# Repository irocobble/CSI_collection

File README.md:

# Human Presence Detection using Wi-Fi CSI

**Team Name: Irocobble_Team** 

## AIM
To develop a prototype device that can sense human presence in a site of interest without using cameras, wearables, or expensive radar hardware. This is achieved by analyzing how Wi-Fi signals change when a person is present.

---

## Research Path — What We Tried First

To achieve human presence detection, our team initially explored IoT devices to detect presence.

1.  **DFRobot C4001 (24 GHz FMCW radar):** This uses a remarkably high frequency of 24 GHz to sense human presence. It works by sending an electromagnetic wave at 24 GHz, and when it reflects back and is captured by the sensor, the wave gets induced by a phase difference. We thought this small phase difference would be enough to accurately detect a human, but these devices require an extremely clean environment to function properly.
2.  **Secondary FMCW IoT Sensor:** We tried a similar IoT device, but it was equally ineffective. Both devices operated on **FMCW (Frequency Modulated Continuous Wave)**. We advise avoiding this approach as it becomes very complicated, although ECE students interested in this can explore it further.

**The Breakthrough:** After failing to extract useful information from these radar devices, we dove deeper and found our solution: **CSI data**.

---

## How It Works — The Big Picture

The system follows a specific pipeline:

**ESP32-S3** → **CSI matrix** → **Spectrogram image** → **EfficientNetV2** → **Activity label** → **Dashboard**

A Wi-Fi router sends signals continuously. The ESP32-S3 acts as the receiver and measures exactly how those signals change as they bounce around the room. When a human moves, they disturb the signal in a unique way. We convert that disturbance into an image (spectrogram) and classify it using a neural network.

---

## Key Definitions

* **CSI (Channel State Information):** Detailed information about how a Wi-Fi signal travels from transmitter to receiver. Unlike RSSI, CSI captures amplitude, phase, and frequency response across every individual subcarrier, providing a rich fingerprint of the environment.
* **OFDM Subcarrier:** Wi-Fi splits its signal into many narrow frequency bands called subcarriers. The ESP32-S3 exposes 52 of them. Each is affected differently by objects in the room, making CSI highly informative.
* **RSSI (Received Signal Strength Indicator):** A single number representing received Wi-Fi signal strength. It is too coarse for detecting subtle human presence compared to CSI.
* **Multipath Propagation:** Wi-Fi signals reflect off walls, furniture, and people, arriving at the receiver via multiple paths. CSI captures all these reflections simultaneously, making it sensitive to human movement.
* **LOS / NLOS (Line-of-Sight / Non-Line-of-Sight):** LOS means a direct path between transmitter and receiver. NLOS means an obstruction blocks the path. Our system works reliably in both conditions.
* **STFT (Short-Time Fourier Transform):** A mathematical tool that converts a 1D signal into a 2D time-frequency image called a spectrogram.
* **Spectrogram:** A grayscale image (52 × 400 pixels in our system) where each column is a snapshot in time and each row is one of the 52 subcarriers. Pixel intensity represents signal amplitude.
* **EfficientNetV2:** A state-of-the-art Convolutional Neural Network (CNN) modified to accept single-channel grayscale spectrograms and retrained on our CSI dataset.
* **FreeRTOS:** A real-time operating system for microcontrollers that lets the ESP32 run tasks concurrently (capturing CSI and sending data over UART) safely.
* **CRC-16/CCITT:** A checksum algorithm that detects transmission errors to ensure clean data enters the pipeline.
* **Hampel Filter:** A statistical outlier-removal filter that replaces sudden noise spikes in the CSI data before transmission.
* **WeightedRandomSampler:** A PyTorch training utility that ensures the model sees each activity class equally often during training to prevent bias.
* **Supabase:** An open-source database used to log every inference result and store spectrogram images.

---

## Hardware

### Why ESP32?
While chips like the Artemis series, BCM series, and some Intel Wi-Fi cards expose CSI, we chose the ESP32 family because it is inexpensive, well-documented, and supported by ESP-IDF (which provides direct access to the CSI callback API).

Our first-generation capture rig used four off-the-shelf ESP32-S3 WROOM modules. We have since designed a **custom dual-receiver PCB** to replace them, described below.

### Custom Dual-Receiver CSI Board (Rev. 2)

Off-the-shelf dev boards proved to be the limiting factor in CSI quality. Their PCB antennas cannot be replaced, their ground planes are shared with USB and power circuitry, and every unit sits on a separate USB cable with its own power supply — all of which inject amplitude noise into exactly the measurement we care about. The custom board addresses each of these.

**Two independent receivers on one board.** Both ESP32s operate in receive-only mode and capture CSI from the same ambient Wi-Fi traffic, giving two spatially separated measurements of the same environment from a single unit.

**Key specifications**

| Item | Detail |
|---|---|
| Board | 4-layer, 55 × 55 mm |
| Stackup | F.Cu / 0.12 mm 2116 prepreg / **In1.Cu solid GND** / 1.165 mm core / **In2.Cu +3V3** / 0.12 mm / B.Cu |
| MCUs | 2 × ESP32, each with its own 40 MHz crystal and AT25SF081 SPI flash |
| Antennas | 2 × SMA connector for external antennas (bi-quad or other) |
| RF feed | 50 Ω controlled-impedance microstrip, 0.20 mm wide |
| Matching | Pi network (1.5 pF / 2 nH / 1.5 pF) per channel, with spare DNP positions for bench tuning |
| USB | USB-C → CH334F hub → 2 × CP2102N UART bridges (one COM port per ESP32) |
| Power | AP63203 buck (5 V → 3.3 V), 2 A polyfuse, PMEG2020EH reverse-protection Schottky |
| Protection | USBLC6-4SC6 ESD array on USB data lines, ESD diodes on EN/BOOT |
| Programming | Cross-coupled DTR/RTS auto-reset per channel (standard esptool circuit) |
| Draw | ~290 mA at 5 V with both receivers active — within the 500 mA USB budget |

**Why the layer stack matters.** A dedicated uninterrupted ground plane 0.12 mm below the signal layer gives every RF and USB trace a clean return path. Nothing is routed on the ground layer. Via inductance from any component to ground is roughly 0.04 nH, so the antenna matching network behaves as designed rather than being swamped by parasitics.

**Antenna launch design.** Each SMA connector is surrounded by a ring of ground vias so the return current reaches the plane immediately. A deliberate void in the ground plane beneath each SMA signal pad removes ~2.3 pF of parasitic capacitance that would otherwise present a 12 Ω discontinuity at the connector. Measured effect: launch insertion loss drops from ~3.3 dB to ~0.1 dB per channel, and both channels are symmetric to within a few tenths of a dB — important when comparing amplitude between the two receivers.

**Single power source.** Both receivers share one regulated 3.3 V rail from a single USB connection, rather than two separately powered dev boards. One cable, one supply, one ground reference.

**Custom Bi-Quad Antenna:** A custom-designed 2.4 GHz directional antenna connects via the SMA ports to provide higher gain and improved CSI stability than a stock PCB antenna.

**Source code and hardware files:** [github.com/irocobble/CSI_collection](https://github.com/irocobble/CSI_collection/tree/main)

### Known Design Limitations

Documented deliberately so future revisions can address them:

* **No cross-receiver phase coherence.** The two ESP32s run from independent crystals, so their carrier and sampling frequency offsets drift relative to each other. This is fine for our amplitude-only pipeline but rules out phase-based techniques such as AoA or MUSIC across the two antennas. A shared 40 MHz TCXO feeding both `XTAL_P` pins would fix this in a future revision.
* **No GPIO breakout.** No general-purpose pins are brought out, so there is no hardware trigger, PPS input, or sync line for correlating CSI against external ground truth. Timestamping is currently done in software over USB.
* **1 MB flash (AT25SF081).** Sufficient for the capture firmware but leaves no room for OTA update partitions.

### Bring-Up Checklist

For anyone assembling a board, test in this order and stop at the first failure — it localises the fault far faster than powering everything at once:

1. **Power only**, no USB data — confirm 3.3 V, check input voltage at the buck, scope the rail for ripple.
2. **Plug USB** — does the hub enumerate? If not, fit the DNP crystal load capacitors (C4/C23, 12 pF).
3. **Check both COM ports appear.** A missing port isolates to that CP2102N or its hub port.
4. **Flash each ESP32** — auto-reset should work without holding buttons.
5. **Scope VDD3P3 during RX.** More than ~50 mV of ripple → populate C8/C42 (1 µF).
6. **VNA the antenna ports** and tune the pi network. This step determines CSI amplitude quality more than anything else.
7. **Capture CSI** and inspect the noise floor across all 52 subcarriers before trusting any measurement.

Keep spare 12 pF 0402, 1 µF 0603, and 12 pF-load 40 MHz crystals on hand for steps 2, 5, and any oscillator trouble.

---

## Firmware — ESP-IDF Setup

### Installation

**Linux**
1.  Make a new directory: `mkdir -p ~/esp`
2.  Get to the directory: `cd ~/esp`
3.  Clone the files from the official ESP git repo:
    `git clone --recursive https://github.com/espressif/esp-idf.git`
4.  Get in the directory: `cd esp-idf`
5.  Install the esp-idf: `./install.sh`

**Windows**
1.  Go to: [https://dl.espressif.com/dl/esp-idf/](https://dl.espressif.com/dl/esp-idf/)
2.  Download and install the universal online installer.

### Activating The Environment
1.  Activate the esp-IDE environment by running export.sh:
    `source ~/esp/esp-idf/export.sh` (Run once per terminal session)
2.  Go to the esp directory: `cd ~/esp`
3.  Run to create an ESP Project: `idf.py create-project my_project`
4.  Go to Project Directory: `cd my_project`

### Required Project File Structure (Crucial!)
The project must follow this layout exactly:

```
my_project/
├── CMakeLists.txt      # lists component directories
├── sdkconfig           # auto-generated after menuconfig
└── main/
    ├── CMakeLists.txt  # registers main.c as a component
    └── main.c          # your application code
```

### Menuconfig (The Heart of ESP-IDE)
Run: `idf.py menuconfig`
Common configurations for this project:
* **Enable CSI:** Component config → Wi-Fi → [*] Enable CSI
* **SSID + Password:** Wi-Fi settings → set the SSID and password.

### Build, Flash, and Monitor
1.  Activate ESP-IDE on bash.
2.  Set the chip target — this **must** match the silicon on the board:
    `idf.py set-target esp32` (use `esp32s3` for the older WROOM-module rig)
3.  Go to the root directory of the Project.
4.  Compile: `idf.py build`
5.  Flash: `idf.py -p /dev/ttyUSB0 flash` (replace port as needed)
6.  Monitor Serial Output: `idf.py monitor` (Ctrl+] to exit)

**Note on the custom board:** it presents **two** serial ports, one per receiver. Flash each independently, e.g. `/dev/ttyUSB0` and `/dev/ttyUSB1`.

### How the Firmware Works
The firmware runs two concurrent FreeRTOS tasks:
1.  **CSI callback:** Fires on every received Wi-Fi packet. Extracts the amplitude of 52 subcarriers, applies a Hampel filter to remove spike outliers, and writes the cleaned sample into a shared frame buffer protected by a FreeRTOS mutex.
2.  **UART TX task:** Once 400 samples accumulate (forming a 52×400 frame), it wraps the payload, computes a CRC-16/CCITT checksum, and transmits at 921,600 baud.

---

## Software Pipeline — Python

### Overview
**Serial read** → **CRC validation** → **Reshape 52×400** → **PNG export** → **API inference** → **Supabase log** → **Dashboard**

* **Serial Ingestion:** A `FrameReader` class maintains a buffer and scans for frames, validating the CRC-16 checksum to ensure clean data.
* **Multi-device Auto-detection:** A background thread scans COM ports to automatically detect active ESP32 units. On the custom board this discovers both on-board receivers as separate ports.
* **Image Construction:** The ESP-32 provides CSI data as a matrix. We convert this 52×400 matrix (200 samples in X-axis and 52 amplitude values in Y-axis) into a 52*400 image. The black and white density represents the amplitude change.
* **Asynchronous Inference & Re-inference:** Python handles real-time inference via an API without blocking the serial reader and includes a GUI for manual re-inference on previously captured frames.

---

## Machine Learning Pipeline

### Dataset
A custom dataset was collected using the four ESP32-S3 units in real indoor environments (LOS and NLOS).
* **Labels:** `trainLabels.csv`, `validationLabels.csv`, `testLabels.csv`
* **Normalization:** `meanStd.csv` is used to apply identical normalization `(x − mean) / std`.

> **Note:** Data captured on the custom board has a different RF front end (external antenna, different ground reference, different launch loss) from the WROOM-module rig. Recompute `meanStd.csv` for the new hardware, and treat the two sources as separate domains until a mixed-hardware model is validated.

### Preprocessing and Augmentation
1.  Grayscale conversion
2.  Tensor conversion ([0, 255] to [0, 1])
3.  Normalization
4.  Random circular shift (training only)
5.  Gaussian noise injection (training only)

### Model (The AI-ML Part)
**Backbone:** EfficientNetV2-S. This is a lightweight, efficient CNN that helps us find key details in the small images we generate. The first convolution layer is modified to accept 1-channel (grayscale) input.

### Training Configuration
* **Loss function:** CrossEntropyLoss
* **Optimiser:** Adam (LR: 0.0001)
* **LR scheduler:** ReduceLROnPlateau
* **Early stopping:** Halts if validation accuracy does not improve for 20 epochs.
* **Class balancing:** WeightedRandomSampler
* **Hardware:** NVIDIA RTX 4060 with CUDA, via PyTorch.

---

## System Integration
* **Flask REST API:** Inference results are served via a Flask REST endpoint.
* **Real-time Web Dashboard:** Displays current activity label and confidence score.
* **Flutter Mobile App:** Cross-platform mobile application mirroring the dashboard.
* **Supabase Cloud Logging:** Every inference result and image is asynchronously inserted into a Supabase Postgres table and storage bucket.

---

## Limitations and Future Work

**Current limitations:** The CNN treats the spectrogram as a static image without explicitly modeling temporal sequences. Performance varies between LOS and NLOS environments when trained exclusively on one. The dataset size is relatively small, and inference currently requires a dedicated PC with a GPU. The custom board's two receivers are amplitude-only and cannot be combined coherently (see Known Design Limitations above).

# Future Work & System Architectures

As the project evolves from a tethered PC-based prototype to a standalone edge-computing device, we are evaluating four distinct architectural paths. Each path offers different trade-offs regarding power consumption, computational capability, and RF flexibility.

## 0. Immediate Next Revision (Rev. 3 of the custom board)
**Concept:** Incremental improvements to the existing dual-receiver design, identified during Rev. 2 design review.
* **Shared clock:** One 40 MHz TCXO buffered to both ESP32s, eliminating relative CFO/SFO and unlocking phase-based processing across the two antennas.
* **GPIO header:** Break out 2–3 pins per chip for external triggering and timestamp synchronisation with ground-truth sensors.
* **Larger flash:** 4 MB part to allow OTA updates in deployed nodes.
* **Per-radio supply filtering:** Ferrite bead and local bulk capacitance on each receiver's 3.3 V feed, so neither radio's supply transients appear in the other's measurement.

## 1. The Microcontroller Ensemble (ESP32-C5 → RP2040 → ESP32-S3)
**Concept:** A fully independent, distributed TinyML system using specialized microcontrollers for each stage of the pipeline.
* **CSI Acquisition (ESP32-C5):** Utilizes dual-band Wi-Fi 6 capabilities. The 5GHz band offers shorter wavelengths, providing higher sensitivity to micro-movements.
* **Signal Processing (RP2040):** Acts as a dedicated DSP to ingest raw amplitude data and perform STFT to generate spectrogram matrices.
* **Inference & IO (ESP32-S3):** Runs a quantized version of the EfficientNetV2 model (via ESP-DL or TFLite Micro) for prediction and drives indication sensors (LEDs, relays, buzzers).
* **Pros:** Ultra-low power, low cost, highly modular, pure edge architecture.
* **Cons:** High risk of data bottlenecks via SPI/UART between three chips. The RP2040 lacks a hardware FPU, potentially slowing down spectrogram generation.

## 2. The Hybrid Edge (ESP32-C5 → Pi Compute Module 5)
**Concept:** Pairing a dedicated CSI sensor with a high-performance Linux edge computer.
* **Workflow:** The ESP32-C5 streams raw CSI data directly to the CM5 via high-speed interfaces. The CM5 handles STFT generation and deep learning inference natively in Python.
* **Pros:** Retains the exact Python/PyTorch software stack currently used on the PC. Massive processing headroom. Eliminates inter-MCU bottlenecks.
* **Cons:** Higher power footprint. Requires designing a custom carrier PCB for the CM5 module.

## 3. High-Resolution MIMO (Intel / Atheros Wi-Fi Cards)
**Concept:** Migrating to standard PCIe Wi-Fi network interface cards running patched Linux kernels (e.g., Linux 802.11n CSI Tool).
* **Workflow:** Utilizing specific chipsets (Intel 5300 or Atheros AR9300) on a Single Board Computer (SBC) to extract highly detailed CSI matrices.
* **Pros:** Unlocks MIMO (Multiple-Input Multiple-Output) data. Capturing multiple spatial streams simultaneously drastically improves environmental mapping and enables directional movement tracking.
* **Cons:** Not scalable as a compact IoT device. Requires painful kernel patching, often locking the system to outdated OS versions and legacy hardware.

## 4. Raw RF Processing (Software Defined Radio - SDR)
**Concept:** Ditching the 802.11 Wi-Fi protocol entirely to capture raw baseband IQ data using hardware like bladeRF or HackRF.
* **Workflow:** Transmitting custom waveforms and analyzing raw reflections without the constraints of Wi-Fi packet structures.
* **Pros:** Ultimate flexibility. Allows operation outside standard Wi-Fi bands (e.g., sub-GHz for superior wall penetration). Total control over bandwidth, modulation, and timing.
* **Cons:** Steep learning curve requiring advanced DSP and RF engineering mathematics. SDRs are expensive and generate massive data throughput requiring significant processing power.
* Edge inference on ESP32-S3 or Jetson Nano
* Multi-node distributed sensing

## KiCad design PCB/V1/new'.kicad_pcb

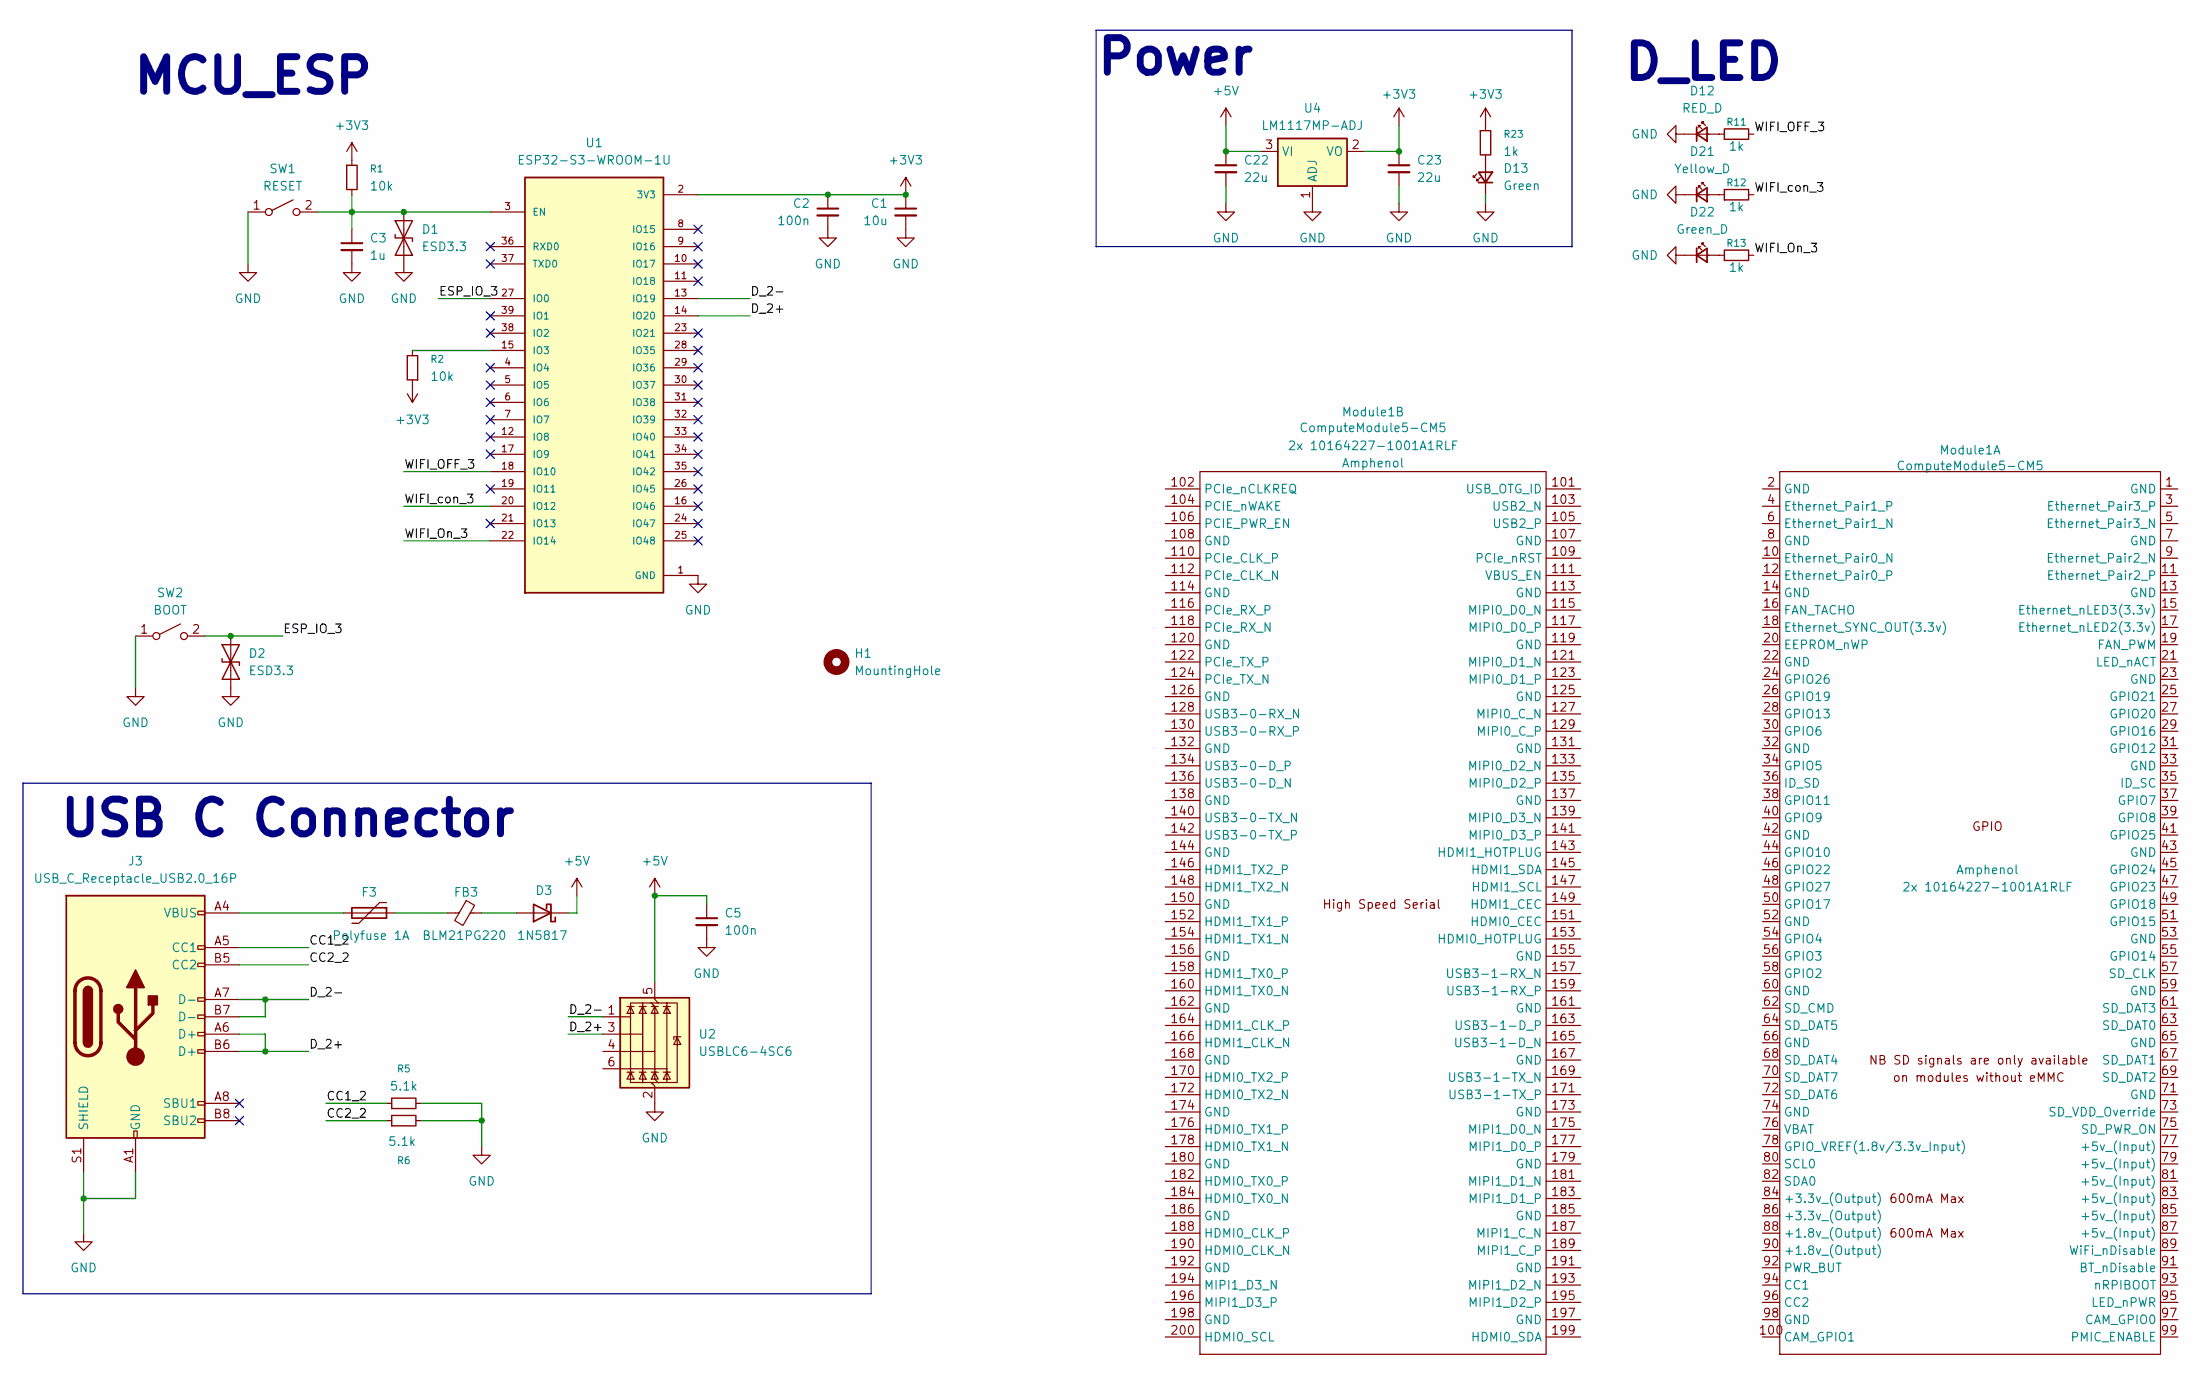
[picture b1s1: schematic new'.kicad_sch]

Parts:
C1: 10u; CAPC1005X55N
C2, C5: 100n; CAPC1005X55N
C3: 1u; CAPC1005X55N
C22, C23: 22u; CAPC1005X55N
D1, D2: ESD3.3; SODFL1006X40N
D3: 1N5817; D_SOD-123
D12: RED_D; LED_0805_2012Metric
D13: Green; LED_0805_2012Metric
D21: Yellow_D; LED_0805_2012Metric
D22: Green_D; LED_0805_2012Metric
F3: Polyfuse 1A; FUSC1608X100N
FB3: BLM21PG220; IND_BLM21_MUR-L
H1: MountingHole; MountingHole_2.2mm_M2_ISO14580_Pad
J3: USB_C_Receptacle_USB2.0_16P; USB_C_Receptacle_HCTL_HC-TYPE-C-16P-01A
Module1: ComputeModule5-CM5; Raspberry-Pi-5-Compute-Module; Part Description 100 Position Connector Receptacle, Cent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
R1, R2: 10k; RC0402N_YAG-L
R5, R6: 5.1k; RC0402N_YAG-L
R11, R12, R13, R23: 1k; RC0402N_YAG-L
SW1: RESET; SW_CS1213AGF260_CRS
SW2: BOOT; SW_CS1213AGF260_CRS
U1: ESP32-S3-WROOM-1U; PARTREV v0.6
U2: USBLC6-4SC6; SOT-23-6
U4: LM1117MP-ADJ; DCY0004A_L

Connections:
+3V3: C1.1, C2.1, C23.1, R1.1, R2.1, R23.1, U1.2 (3V3), U4.2 (VO)
+5V: C5.1, C22.1, D3.1 (K), U2.5 (VBUS), U4.3 (VI)
/CC1_2: J3.A5 (CC1), R5.1
/CC2_2: J3.B5 (CC2), R6.1
/D_2+: J3.A6 (D+), J3.B6 (D+), U1.14 (IO20), U2.3 (I/O2)
/D_2-: J3.A7 (D-), J3.B7 (D-), U1.13 (IO19), U2.1 (I/O1)
/ESP_IO_3: D2.2 (A2), SW2.2 (B), U1.27 (IO0)
/WIFI_OFF_3: R11.2, U1.18 (IO10)
/WIFI_On_3: R13.2, U1.22 (IO14)
/WIFI_con_3: R12.2, U1.20 (IO12)
GND: C1.2, C2.2, C3.2, C5.2, C22.2, C23.2, D1.1 (A1), D2.1 (A1), D12.1 (K), D13.1 (K), D21.1 (K), D22.1 (K), J3.A1 (GND), J3.A12 (GND), J3.B1 (GND), J3.B12 (GND), J3.S1 (SHIELD), R5.2, R6.2, SW1.1 (A), SW2.1 (A), U1.1 (GND), U1.40 (GND), U1.41_1 (GND), U1.41_2 (GND), U1.41_3 (GND), U1.41_4 (GND), U1.41_5 (GND), U1.41_6 (GND), U1.41_7 (GND), U1.41_8 (GND), U1.41_9 (GND), U2.2 (GND), U4.1 (ADJ)
unnamed: C3.1, D1.2 (A2), R1.2, SW1.2 (B), U1.3 (EN)
unnamed: D3.2 (A), FB3.1
unnamed: D12.2 (A), R11.1
unnamed: D13.2 (A), R23.2
unnamed: D21.2 (A), R12.1
unnamed: D22.2 (A), R13.1
unnamed: F3.1, FB3.2
unnamed: F3.2, J3.A4 (VBUS), J3.A9 (VBUS), J3.B4 (VBUS), J3.B9 (VBUS)
unnamed: R2.2, U1.15 (IO3)

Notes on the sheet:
MCU_ESP
Power
D_LED
USB C Connector

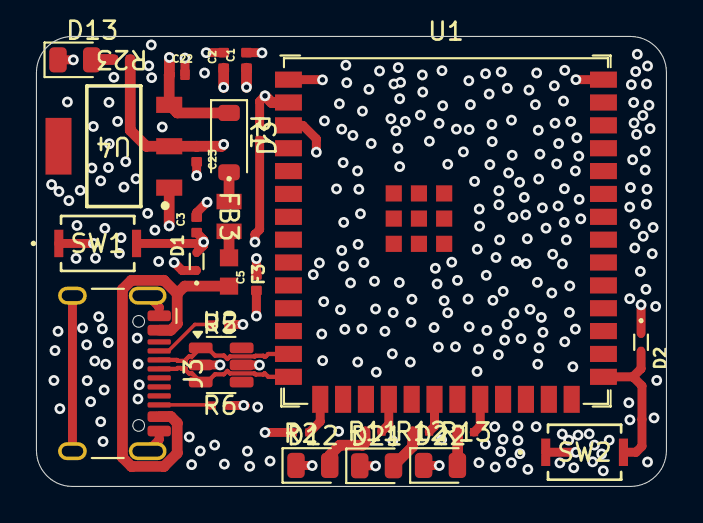
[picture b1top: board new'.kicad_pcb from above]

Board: 4 copper layers, 35.0 x 25.0 mm, 29 parts (0 on the bottom side), 20 nets.

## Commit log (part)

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2026-04-03 This add the PCB design
2026-04-06 Add files via upload
    added Program code for extracting CSI data from Wroom 32
2026-04-06 added an stop button
2026-04-06 Refactor import.py to modularize functions and settings, to new supabase working code
2026-04-06 supabase , image upload error, due to file name , solved
2026-04-07 added a stop and resume button
